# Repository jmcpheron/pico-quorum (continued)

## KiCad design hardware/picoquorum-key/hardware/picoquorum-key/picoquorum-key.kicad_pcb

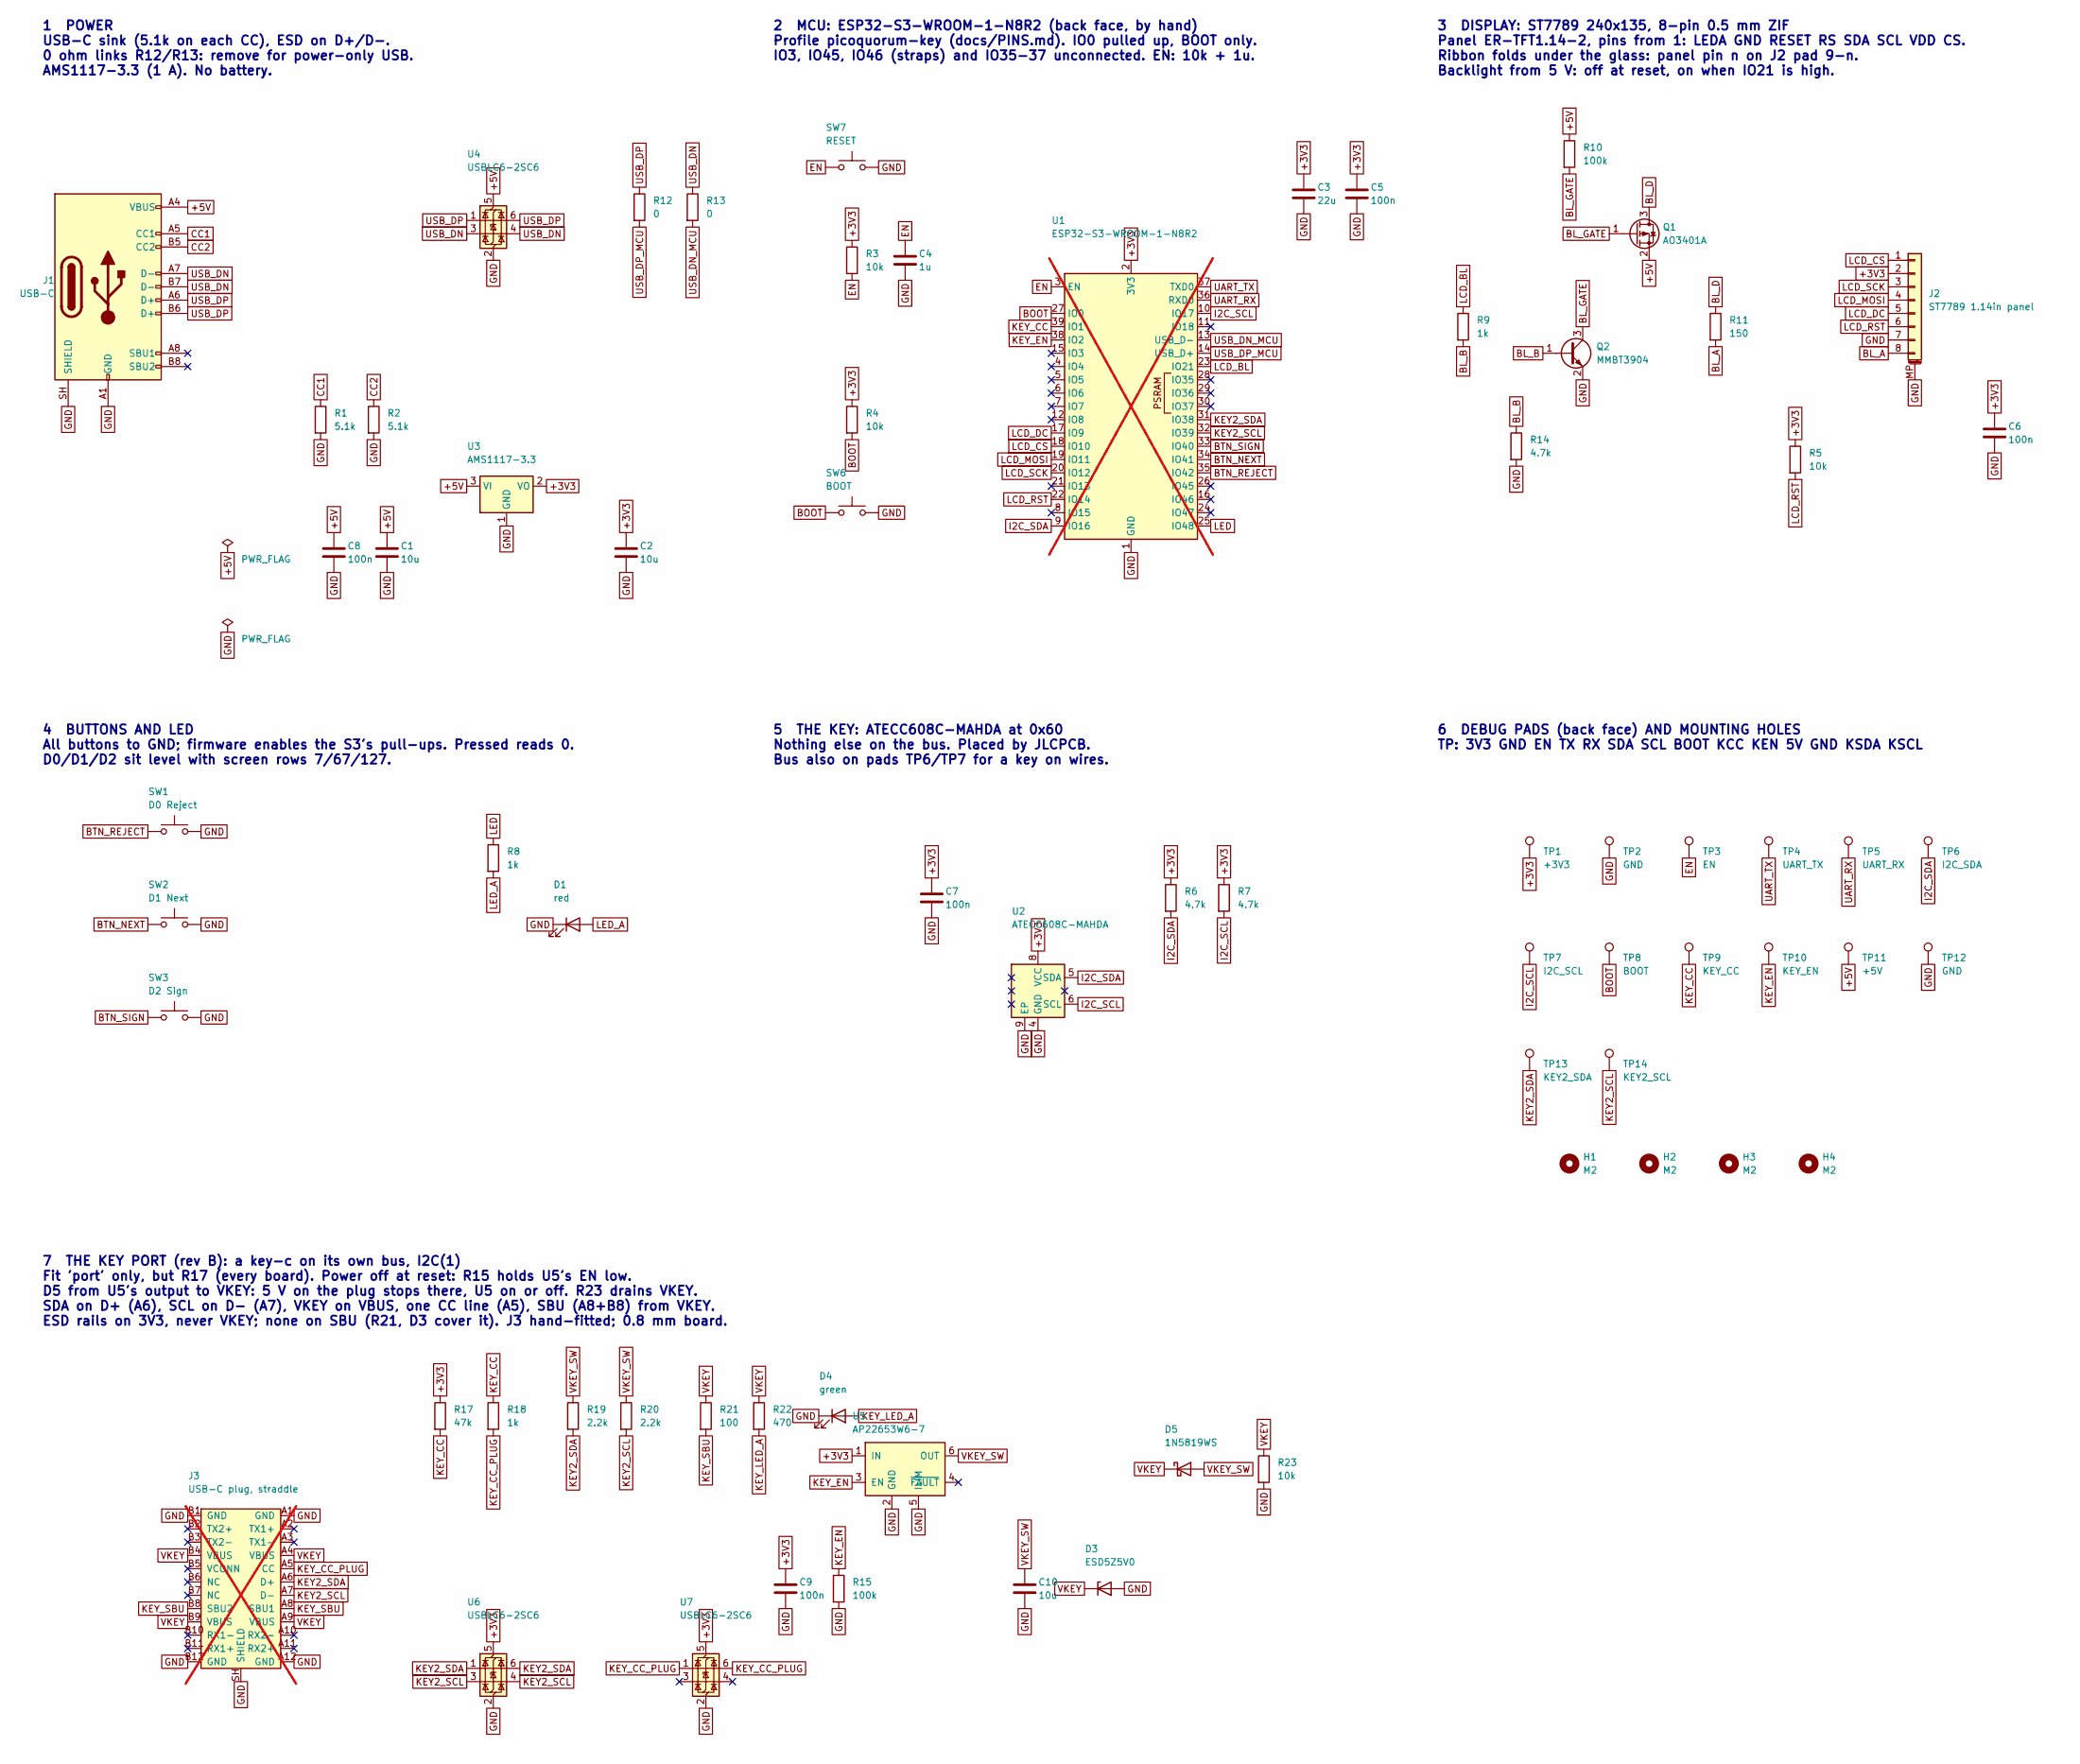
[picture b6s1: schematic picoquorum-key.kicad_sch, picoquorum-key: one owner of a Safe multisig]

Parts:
C1, C2, C10: 10u; C_0805_2012Metric; MPN 10u; LCSC C15850
C3: 22u; C_0805_2012Metric; MPN 22u; LCSC C45783
C4: 1u; C_0603_1608Metric; MPN 1u; LCSC C15849
C5, C6, C7, C8, C9: 100n; C_0603_1608Metric; MPN 100n; LCSC C14663
D1: red; LED_0603_1608Metric; MPN KT-0603R; LCSC C2286
D3: ESD5Z5V0; D_SOD-523; MPN ESD5Z5V0; LCSC C502546
D4: green; LED_0603_1608Metric; MPN KT-0603G; LCSC C12624
D5: 1N5819WS; D_SOD-323; MPN 1N5819WS; LCSC C191023
H1, H2, H3, H4: M2; MountingHole_2.2mm_M2; MPN M2
J1: USB-C; USB_C_Receptacle_HRO_TYPE-C-31-M-12_Edge; MPN HRO TYPE-C-31-M-12; LCSC C165948
J2: ST7789 1.14in panel; FPC_0.5mm_8P_C2919492; MPN HDGC 0.5K-HX-8PWB; LCSC C2919492
J3: USB-C plug, straddle; USB_C_Plug_ShouHan_24P-GTJB_Straddle; MPN TYPE-C 24P-GTJB 040; LCSC C3151751; not fitted
Q1: AO3401A; SOT-23; MPN AO3401A; LCSC C15127
Q2: MMBT3904; SOT-23; MPN MMBT3904; LCSC C20526
R1, R2: 5.1k; R_0603_1608Metric; MPN 5.1k; LCSC C23186
R3, R4, R5, R23: 10k; R_0603_1608Metric; MPN 10k; LCSC C25804
R6, R7, R14: 4.7k; R_0603_1608Metric; MPN 4.7k; LCSC C23162
R8, R9, R18: 1k; R_0603_1608Metric; MPN 1k; LCSC C21190
R10, R15: 100k; R_0603_1608Metric; MPN 100k; LCSC C25803
R11: 150; R_0603_1608Metric; MPN 150; LCSC C22808
R12, R13: 0; R_0603_1608Metric; MPN 0; LCSC C21189
R17: 47k; R_0603_1608Metric; MPN 47k; LCSC C25819
R19, R20: 2.2k; R_0603_1608Metric; MPN 2.2k; LCSC C4190
R21: 100; R_0603_1608Metric; MPN 100; LCSC C22775
R22: 470; R_0603_1608Metric; MPN 470; LCSC C23179
SW1: D0 Reject; SW_Tact_4.5x4.5_C2897501; MPN BOOMELE 4.5x4.5x3.8 SMD tact; LCSC C2897501
SW2: D1 Next; SW_Tact_4.5x4.5_C2897501; MPN BOOMELE 4.5x4.5x3.8 SMD tact; LCSC C2897501
SW3: D2 Sign; SW_Tact_4.5x4.5_C2897501; MPN BOOMELE 4.5x4.5x3.8 SMD tact; LCSC C2897501
SW6: BOOT; SW_Tact_4.5x4.5_C2897501; MPN BOOMELE 4.5x4.5x3.8 SMD tact; LCSC C2897501
SW7: RESET; SW_Tact_4.5x4.5_C2897501; MPN BOOMELE 4.5x4.5x3.8 SMD tact; LCSC C2897501
TP1: +3V3; TestPoint_Pad_1.5x1.5mm; MPN +3V3
TP2, TP12: GND; TestPoint_Pad_1.5x1.5mm; MPN GND
TP3: EN; TestPoint_Pad_1.5x1.5mm; MPN EN
TP4: UART_TX; TestPoint_Pad_1.5x1.5mm; MPN UART_TX
TP5: UART_RX; TestPoint_Pad_1.5x1.5mm; MPN UART_RX
TP6: I2C_SDA; TestPoint_Pad_1.5x1.5mm; MPN I2C_SDA
TP7: I2C_SCL; TestPoint_Pad_1.5x1.5mm; MPN I2C_SCL
TP8: BOOT; TestPoint_Pad_1.5x1.5mm; MPN BOOT
TP9: KEY_CC; TestPoint_Pad_1.5x1.5mm; MPN KEY_CC
TP10: KEY_EN; TestPoint_Pad_1.5x1.5mm; MPN KEY_EN
TP11: +5V; TestPoint_Pad_1.5x1.5mm; MPN +5V
TP13: KEY2_SDA; TestPoint_Pad_1.5x1.5mm; MPN KEY2_SDA
TP14: KEY2_SCL; TestPoint_Pad_1.5x1.5mm; MPN KEY2_SCL
U1: ESP32-S3-WROOM-1-N8R2; ESP32-S3-WROOM-1_HandSolder; MPN ESP32-S3-WROOM-1-N8R2; LCSC C2913204; not fitted
U2: ATECC608C-MAHDA; DFN-8-1EP_3x2mm_P0.5mm_EP1.3x1.5mm; MPN ATECC608C-MAHDA-S; LCSC C23291019
U3: AMS1117-3.3; SOT-223-3_TabPin2; MPN AMS1117-3.3; LCSC C6186
U4, U6, U7: USBLC6-2SC6; SOT-23-6; MPN USBLC6-2SC6; LCSC C7519
U5: AP22653W6-7; SOT-23-6; MPN AP22653W6-7; LCSC C2158037

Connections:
+3V3: C2.1, C3.1, C5.1, C6.1, C7.1, C9.1, J2.2, R3.1, R4.1, R5.1, R6.1, R7.1, R17.1, TP1.1, U1.2 (3V3), U2.8 (VCC), U3.2 (VO), U5.1 (IN), U6.5 (VBUS), U7.5 (VBUS)
+5V: C1.1, C8.1, J1.A4 (VBUS), J1.A9 (VBUS), J1.B4 (VBUS), J1.B9 (VBUS), Q1.2 (S), R10.1, TP11.1, U3.3 (VI), U4.5 (VBUS)
BL_A: J2.8, R11.2
BL_B: Q2.1 (B), R9.2, R14.1
BL_D: Q1.3 (D), R11.1
BL_GATE: Q1.1 (G), Q2.3 (C), R10.2
BOOT: R4.2, SW6.1, TP8.1, U1.27 (IO0)
BTN_NEXT: SW2.1, U1.34 (IO41)
BTN_REJECT: SW1.1, U1.35 (IO42)
BTN_SIGN: SW3.1, U1.33 (IO40)
CC1: J1.A5 (CC1), R1.1
CC2: J1.B5 (CC2), R2.1
EN: C4.1, R3.2, SW7.1, TP3.1, U1.3 (EN)
GND: C1.2, C2.2, C3.2, C4.2, C5.2, C6.2, C7.2, C8.2, C9.2, C10.2, D1.1 (K), D3.2 (A), D4.1 (K), J1.A1 (GND), J1.A12 (GND), J1.B1 (GND), J1.B12 (GND), J1.SH (SHIELD), J2.7, J2.MP (MountPin), J3.A1 (GND), J3.A12 (GND), J3.B1 (GND), J3.B12 (GND), J3.SH (SHIELD), Q2.2 (E), R1.2, R2.2, R14.2, R15.2, R23.2, SW1.2, SW2.2, SW3.2, SW6.2, SW7.2, TP2.1, TP12.1, U1.1 (GND), U1.40 (GND), U1.41 (GND), U2.4 (GND), U2.9 (EP), U3.1 (GND), U4.2 (GND), U5.2 (GND), U5.5 (ILIM), U6.2 (GND), U7.2 (GND)
I2C_SCL: R7.2, TP7.1, U1.10 (IO17), U2.6 (SCL)
I2C_SDA: R6.2, TP6.1, U1.9 (IO16), U2.5 (SDA)
KEY2_SCL: J3.A7 (D-), R20.2, TP14.1, U1.32 (IO39), U6.3 (I/O2), U6.4 (I/O2)
KEY2_SDA: J3.A6 (D+), R19.2, TP13.1, U1.31 (IO38), U6.1 (I/O1), U6.6 (I/O1)
KEY_CC: R17.2, R18.1, TP9.1, U1.39 (IO1)
KEY_CC_PLUG: J3.A5 (CC), R18.2, U7.1 (I/O1), U7.6 (I/O1)
KEY_EN: R15.1, TP10.1, U1.38 (IO2), U5.3 (EN)
KEY_LED_A: D4.2 (A), R22.2
KEY_SBU: J3.A8 (SBU1), J3.B8 (SBU2), R21.2
LCD_BL: R9.1, U1.23 (IO21)
LCD_CS: J2.1, U1.18 (IO10)
LCD_DC: J2.5, U1.17 (IO9)
LCD_MOSI: J2.4, U1.19 (IO11)
LCD_RST: J2.6, R5.2, U1.22 (IO14)
LCD_SCK: J2.3, U1.20 (IO12)
LED: R8.1, U1.25 (IO48)
LED_A: D1.2 (A), R8.2
UART_RX: TP5.1, U1.36 (RXD0)
UART_TX: TP4.1, U1.37 (TXD0)
USB_DN: J1.A7 (D-), J1.B7 (D-), R13.1, U4.3 (I/O2), U4.4 (I/O2)
USB_DN_MCU: R13.2, U1.13 (USB_D-)
USB_DP: J1.A6 (D+), J1.B6 (D+), R12.1, U4.1 (I/O1), U4.6 (I/O1)
USB_DP_MCU: R12.2, U1.14 (USB_D+)
VKEY: D3.1 (K), D5.1 (K), J3.A4 (VBUS), J3.A9 (VBUS), J3.B4 (VBUS), J3.B9 (VBUS), R21.1, R22.1, R23.1
VKEY_SW: C10.1, D5.2 (A), R19.1, R20.1, U5.6 (OUT)

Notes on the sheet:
1 POWER USB-C sink (5.1k on each CC), ESD on D+/D-. 0 ohm links R12/R13: remove for power-only USB. AMS1117-3.3 (1 A). No battery.
2 MCU: ESP32-S3-WROOM-1-N8R2 (back face, by hand) Profile picoquorum-key (docs/PINS.md). IO0 pulled up, BOOT only. IO3, IO45, IO46 (straps) and IO35-37 unconnected. EN: 10k + 1u.
3 DISPLAY: ST7789 240x135, 8-pin 0.5 mm ZIF Panel ER-TFT1.14-2, pins from 1: LEDA GND RESET RS SDA SCL VDD CS. Ribbon folds under the glass: panel pin n on J2 pad 9-n. Backlight from 5 V: off at reset, on when IO21 is high.
4 BUTTONS AND LED All buttons to GND; firmware enables the S3's pull-ups. Pressed reads 0. D0/D1/D2 sit level with screen rows 7/67/127.
5 THE KEY: ATECC608C-MAHDA at 0x60 Nothing else on the bus. Placed by JLCPCB. Bus also on pads TP6/TP7 for a key on wires.
6 DEBUG PADS (back face) AND MOUNTING HOLES TP: 3V3 GND EN TX RX SDA SCL BOOT KCC KEN 5V GND KSDA KSCL
7 THE KEY PORT (rev B): a key-c on its own bus, I2C(1) Fit 'port' only, but R17 (every board). Power off at reset: R15 holds U5's EN low. D5 from U5's output to VKEY: 5 V on the plug stops there, U5 on or off. R23 drains VKEY. SDA on D+ (A6), SCL on D- (A7), VKEY on VBUS, one CC line (A5), SBU (A8+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

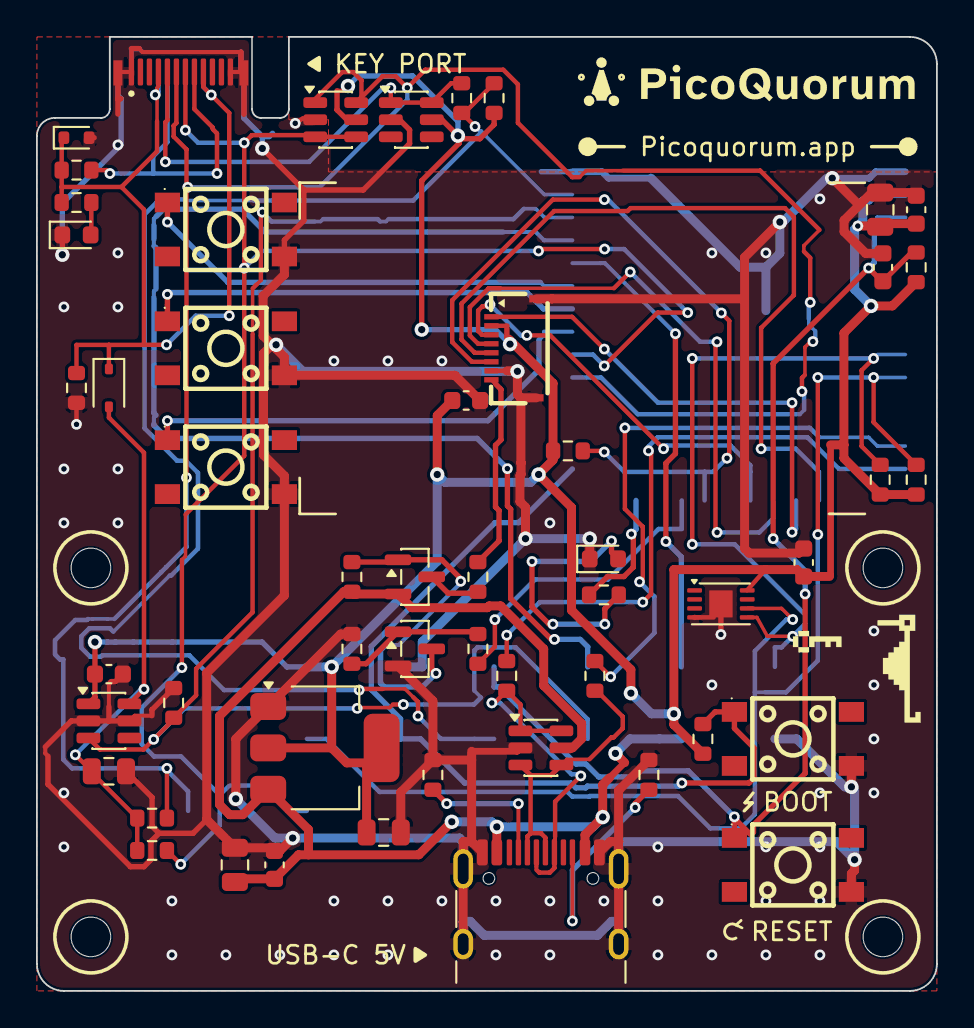
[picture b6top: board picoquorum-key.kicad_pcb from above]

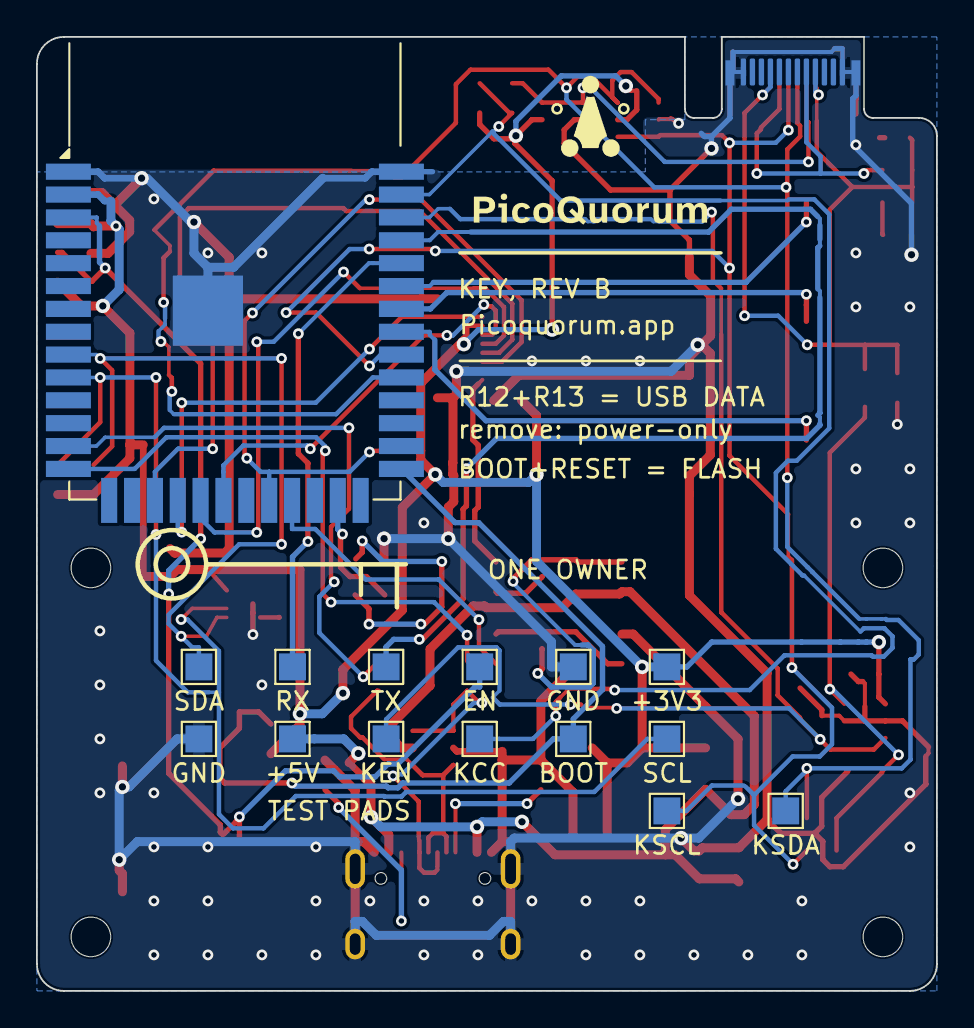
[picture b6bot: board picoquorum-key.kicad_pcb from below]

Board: 2 copper layers, 50.0 x 53.0 mm, 71 parts (15 on the bottom side), 39 nets.

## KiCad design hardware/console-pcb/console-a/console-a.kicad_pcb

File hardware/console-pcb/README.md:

# Console PCB, concept 1

The separate [M1 prototype carrier](../console-pcb-m1/README.md) has a 1.3 inch
colour LCD module, eight SMT buttons, a Pico 2 W module and internal key-adapter
pads. Its routed KiCad files and manufacturing quote package are separate from
the earlier knob/dock concept and CAD studies below.

2026-10-07. **Design in progress, not fabrication files.** A controls subcircuit and
native KiCad placement study now exist. The complete schematic, routing, physical fit
and hardware tests are unfinished. Do not order from these drafts.

Start with [component research and CAD status](RESEARCH.md). The
[controls drawing](review/controls.svg) comes from `controls.kicad_sch`; the
[placement drawing](review/placement.svg) comes from `placement-study.kicad_pcb`.
They are separate studies, not a schematic/PCB pair ready for manufacturing.

The chosen direction is a colour screen, a rotary knob, and a USB-C key dock. Favour
straightforward assembly and supported parts over the lowest component price. Start with
external power and no battery. Quantities to quote later: 5 prototypes, 20 and 100 consoles.

## Face and case

The sketch proposes a 130 x 110 mm case and a 120 x 100 mm main PCB. These are layout
allowances, not measured component fits. Case height is open until the display, plug,
encoder and Pico stack is drawn in section. The face is horizontal for this first study.

| item | proposed allowance | detail still to settle |
|---|---|---|
| Screen, left | 70 x 51 mm panel envelope | 2.8 inch colour, 320 x 240 landscape; exact panel and ribbon exit |
| Knob, right | 24 mm diameter cap | shaft length, detents, push force and support |
| Key dock, back right | 22 x 25 mm footprint | upright insertion; pocket must fit the final key case |
| Sign and Reject, front left | 12 mm button caps | Sign recessed behind a rim; Reject unobstructed |
| Back and Device, front right | two smaller buttons | preserve B and X functions while the UI is reviewed |
| Power, back | USB-C female socket | separate from the male key dock; label POWER |

The ordered key is a 16 x 36 mm PCB with a female connector. It stands upright in this
proposal. Its case, finger clearance and insertion path need a side-view fit study. The
dock footprint is not the key's full height. Do not change the ordered P2 key board.

Support the key case with guide walls. Keep the plug below their rim. Use a stop and
clearance stack based on the connector's mating drawing: the pocket must allow full
mating without forcing the connector past its travel. Allow easy one-hand removal;
no locking latch in this revision. Support the main PCB near the plug and encoder.
The solder pads must not be the only path for insertion or sideways loads.

The panel mounts to the case with a compliant support. Insert its ribbon into a locking
connector after soldering. Do not load the glass or fold its ribbon sharply. Place the
Pico antenna at an enclosure edge, with the manufacturer's copper/component keepout and
clearance from the display, key, metal knob and case hardware. The sketch does not place
the Pico or establish that these clearances fit.

## Parts to evaluate

These are candidates and requirements, not a purchasing BOM. Stock, full order codes,
footprints, assembly availability and mating dimensions remain to be checked.

| function | candidate or requirement | reason / open point |
|---|---|---|
| Processor | Raspberry Pi Pico 2 W, without headers | existing firmware; castellated carrier mounting; assembler must accept the module and thermal process |
| Encoder | Bourns PEC11J, detented version with push switch | SMD; choose full shaft/detent/switch code after a feel sample |
| Key plug | GCT USB4151 vertical Type-C plug family | documented docking part; 24 contacts, SMD signal terminals and through-hole shell stakes; confirm exact version and process |
| Screen | 2.8 inch, 240 x 320 native, four-wire SPI ST7789, no touch | prefer wide viewing angles and a locking FPC connector; exact part unselected |
| Screen comparison | EastRising ER-TFT028A3-4 | documented plug-in FPC and 50.20 x 69.30 mm outline; directional viewing, so not an IPS selection |
| Buttons | documented SMT tactile switches and case-held caps | separate A, B, X and Y; full part and actuation force open |
| Power input | USB-C receptacle, 5 V sink, no PD negotiation | independent Rd on each CC; input protection and current budget needed |
| Key power | current-limited, reverse-blocking switch, default off | TPS2553 family is a comparison candidate, not selected; its 75 mA typical lower limit and fault behaviour require review |
| Bus protection | bidirectional isolation with powered-off and foreign-voltage protection, plus connector ESD protection | exact parts open; preserve ATECC wake timing and open-drain signalling |

The PEC11J datasheet specifies 100,000 rotational cycles and 20,000 switch cycles. It
calls for one reflow pass, discourages hand soldering, and does not recommend aqueous
washing. Agree the assembly sequence before layout. A mostly single-side assembly is
a goal, not a constraint that overrides mechanical support or antenna clearance.

The working encoder choice is now PEC11J-9215F-S0015; its 30 detents / 15 pulses
need a click-count check with the current driver. The four working button choices
are TL3305AF160QG. Full findings and assembly limits are in [RESEARCH.md](RESEARCH.md).
The USB4151 drawing specifies a 0.8 mm board. A small supported dock board is under
consideration so the main board can stay 1.6 mm; its stack and internal connection
are not yet designed.

The display comparison part lists 2.8 V typical supply and 70 mA typical backlight
current. It is not a drop-in replacement for the bench display module. Check logic
levels, supply limits, SPI mode straps and LED wiring in the exact datasheet before
choosing regulators or a backlight driver. GP13 controls the driver; it does not power
the LED string. A new panel still needs colour, orientation and readability checks.

## Circuit blocks

```text
Rear POWER socket (5 V)
    -> input protection and supply isolation -> Pico VSYS
    -> display supplies / backlight driver (after panel selection)

Pico 3V3 -> default-off, current-limited, reverse-blocking switch -> KEY_VCC
KEY_VCC -> dock VBUS; controlled discharge; key-side bus pull-ups

GP4/GP5 <-> protected, isolatable I2C path <-> dock D+/D- <-> key SDA/SCL
Dock attachment contacts -> protected sensing -> presence / fault handling
GP6 -> key power request; hardware fault conditions must override it

GP8..GP13 -> display control and SPI; GP13 -> backlight driver control
GP3/GP2/GP1 <- encoder A/B/push
GP15/GP17/GP19/GP21 <- Sign/Back/Device/Reject
```

This is a functional diagram, not a wireable schematic. Check the Pico regulator's
available current under Wi-Fi load before assigning display and key loads to 3V3.
Keep a service route to Pico BOOTSEL, RUN and SWD. If Pico micro-USB remains accessible,
the external supply arrangement must tolerate both power inputs without backfeeding.

### The key port

The port uses Type-C mechanics but carries I2C and switched 3.3 V, not USB data or a
standard USB power-source interface. Never connect dock VBUS straight to GP6, 3V3 or 5 V.

The existing [socket-and-cable proposal](../key-pcb/PROPOSALS.md#the-console-end-of-key-c)
is background, not a direct-plug schematic. A plug has CC/VCONN roles that differ from
a receptacle's CC1/CC2 arrangement. Trace the selected plug and the P2 receptacle pin
by pin, in both orientations. Do not copy the rule "exactly one Rd" from the cable
proposal without establishing what this mating pair actually exposes. Do not tie
attachment-sense contacts together or energize VCONN by assumption.

Required behaviour:

- Power and bus drive default off during reset, boot, removal and fault.
- Stable attachment permits controlled power-up. It does not authenticate a key or
  prove full mechanical seating. Confirm the chip and reject unsupported devices.
- Removal cancels an unfinished approval, cuts power and releases the bus. Reinserted
  keys must not inherit the previous review or hold-to-sign state.
- Limit short-circuit current in hardware. Validate switch tolerance, startup current,
  thermal behaviour and shutdown; do not equate the limit with normal key current.
- Block foreign VBUS from the console supply, both powered and unpowered. A load switch
  alone does not protect SDA, SCL or the attachment-sense inputs.
- Isolate MCU bus pins from externally driven voltages and an unpowered key. Start with
  the earlier 2.2 kohm switched pull-up proposal only as a value to calculate and measure.
  External VBUS must not turn those pull-ups into a path to an unprotected GPIO.
- Protect exposed contacts against ESD. ESD suppression is not sustained overvoltage
  protection. Specify the charger/adapter fault envelope before choosing devices.
- Controlled discharge must not short an externally powered VBUS. Check this explicitly.

## Proposed GPIO reservation

Preserve current `firmware/board.py` assignments where possible. Nothing changes firmware
in this draft. In particular, the knob A/B naming below follows the current driver,
whose ordering differs from the older breadboard labels.

| GPIO | proposed function |
|---|---|
| 1 | encoder push; maintenance at boot |
| 3, 2 | encoder A, B; verify direction and steps per detent on selected part |
| 4, 5 | key SDA, SCL through protection |
| 6 | key power request, external default-off bias |
| 7 | reserved for attachment/fault logic |
| 8, 9, 10, 11, 12, 13 | display DC, CS, SCK, MOSI, RESET, backlight control |
| 15, 17, 19, 21 | A/Sign, B/Back, X/Device, Y/Reject; Y also Wi-Fi setup at boot |
| 26, 27 | reserve for protected attachment sensing if analog sensing is chosen |
| 28 | spare analog input; no battery in this revision |

GP26/27 are reassigned from the old Build 1 Trust M reset / key-ID plan. Do not use
this draft with that harness. No console signing, key provisioning or lock behaviour
changes are authorized by this design document.

## Before a manufacturing quote

1. Select the exact display, plug, encoder and switches. Obtain drawings and check
   assembler stock or sourcing, packaging and solder process. Resolve the power budget.
2. Draw the electrical schematic, including the actual plug pin map and all fault paths.
   Review every powered/unpowered combination and check the firmware work required.
3. Draw the mechanical stack and print a dock/knob fit sample. Check actual key-case fit,
   full connector engagement, removal, board flex and antenna clearance.
4. Route the PCB with mounting holes, test access and source-location silkscreen. Run
   ERC, DRC, connectivity and schematic/PCB parity checks; inspect footprints and 3D fit.
5. Export Gerbers, drills, BOM, placement file, assembly drawings and STEP models. Quote
   5/20/100 separately, including module installation, screen insertion, enclosure,
   programming and testing. A quote is not permission to place an order.

Before a production batch, bench-check controlled startup, short and foreign-power
faults, hot removal, both key orientations, bus rise time and wake timing. Exercise the
complete review/reject/hold-to-sign flow on test keys. Do not provision, lock or write
hardware without a separate explicit request. The signing site remains `quorum.sign_it`.

## Sources and checks

Manufacturer pages checked 2026-10-07:

- [Pico 2 W](https://www.raspberrypi.com/products/raspberry-pi-pico-2/?variant=pico-2-w).
- [PEC11J datasheet](https://www.bourns.com/docs/product-datasheets/pec11j.pdf).
- [GCT plug selector](https://gct.co/usb-connector/usb-plug) and
  [USB4151 introduction](https://gct.co/news/gct-launches-vertical-mount-usb-type-c-plug-aimed-at-docking-designs).
- [Display comparison](https://www.buydisplay.com/2-8-inch-tft-lcd-display-capacitive-touch-screen-st7789v-spi-240x320).
- [TPS2553 family datasheet](https://www.ti.com/lit/ds/symlink/tps2553.pdf).

Read against the repository README, hardware notes, ordered key-C P2 description,
Build 1 pin map, `firmware/board.py`, `firmware/knob.py` and console button handling.
The concept drawing is an editable SVG. Its panel and control shapes are layout
envelopes, not component footprints. See [CHECKS.md](CHECKS.md) for the controls ERC,
placement DRC findings and the checks still missing. No supplier stock, assembly
quote, circuit simulation, physical fit or hardware behaviour has been verified.

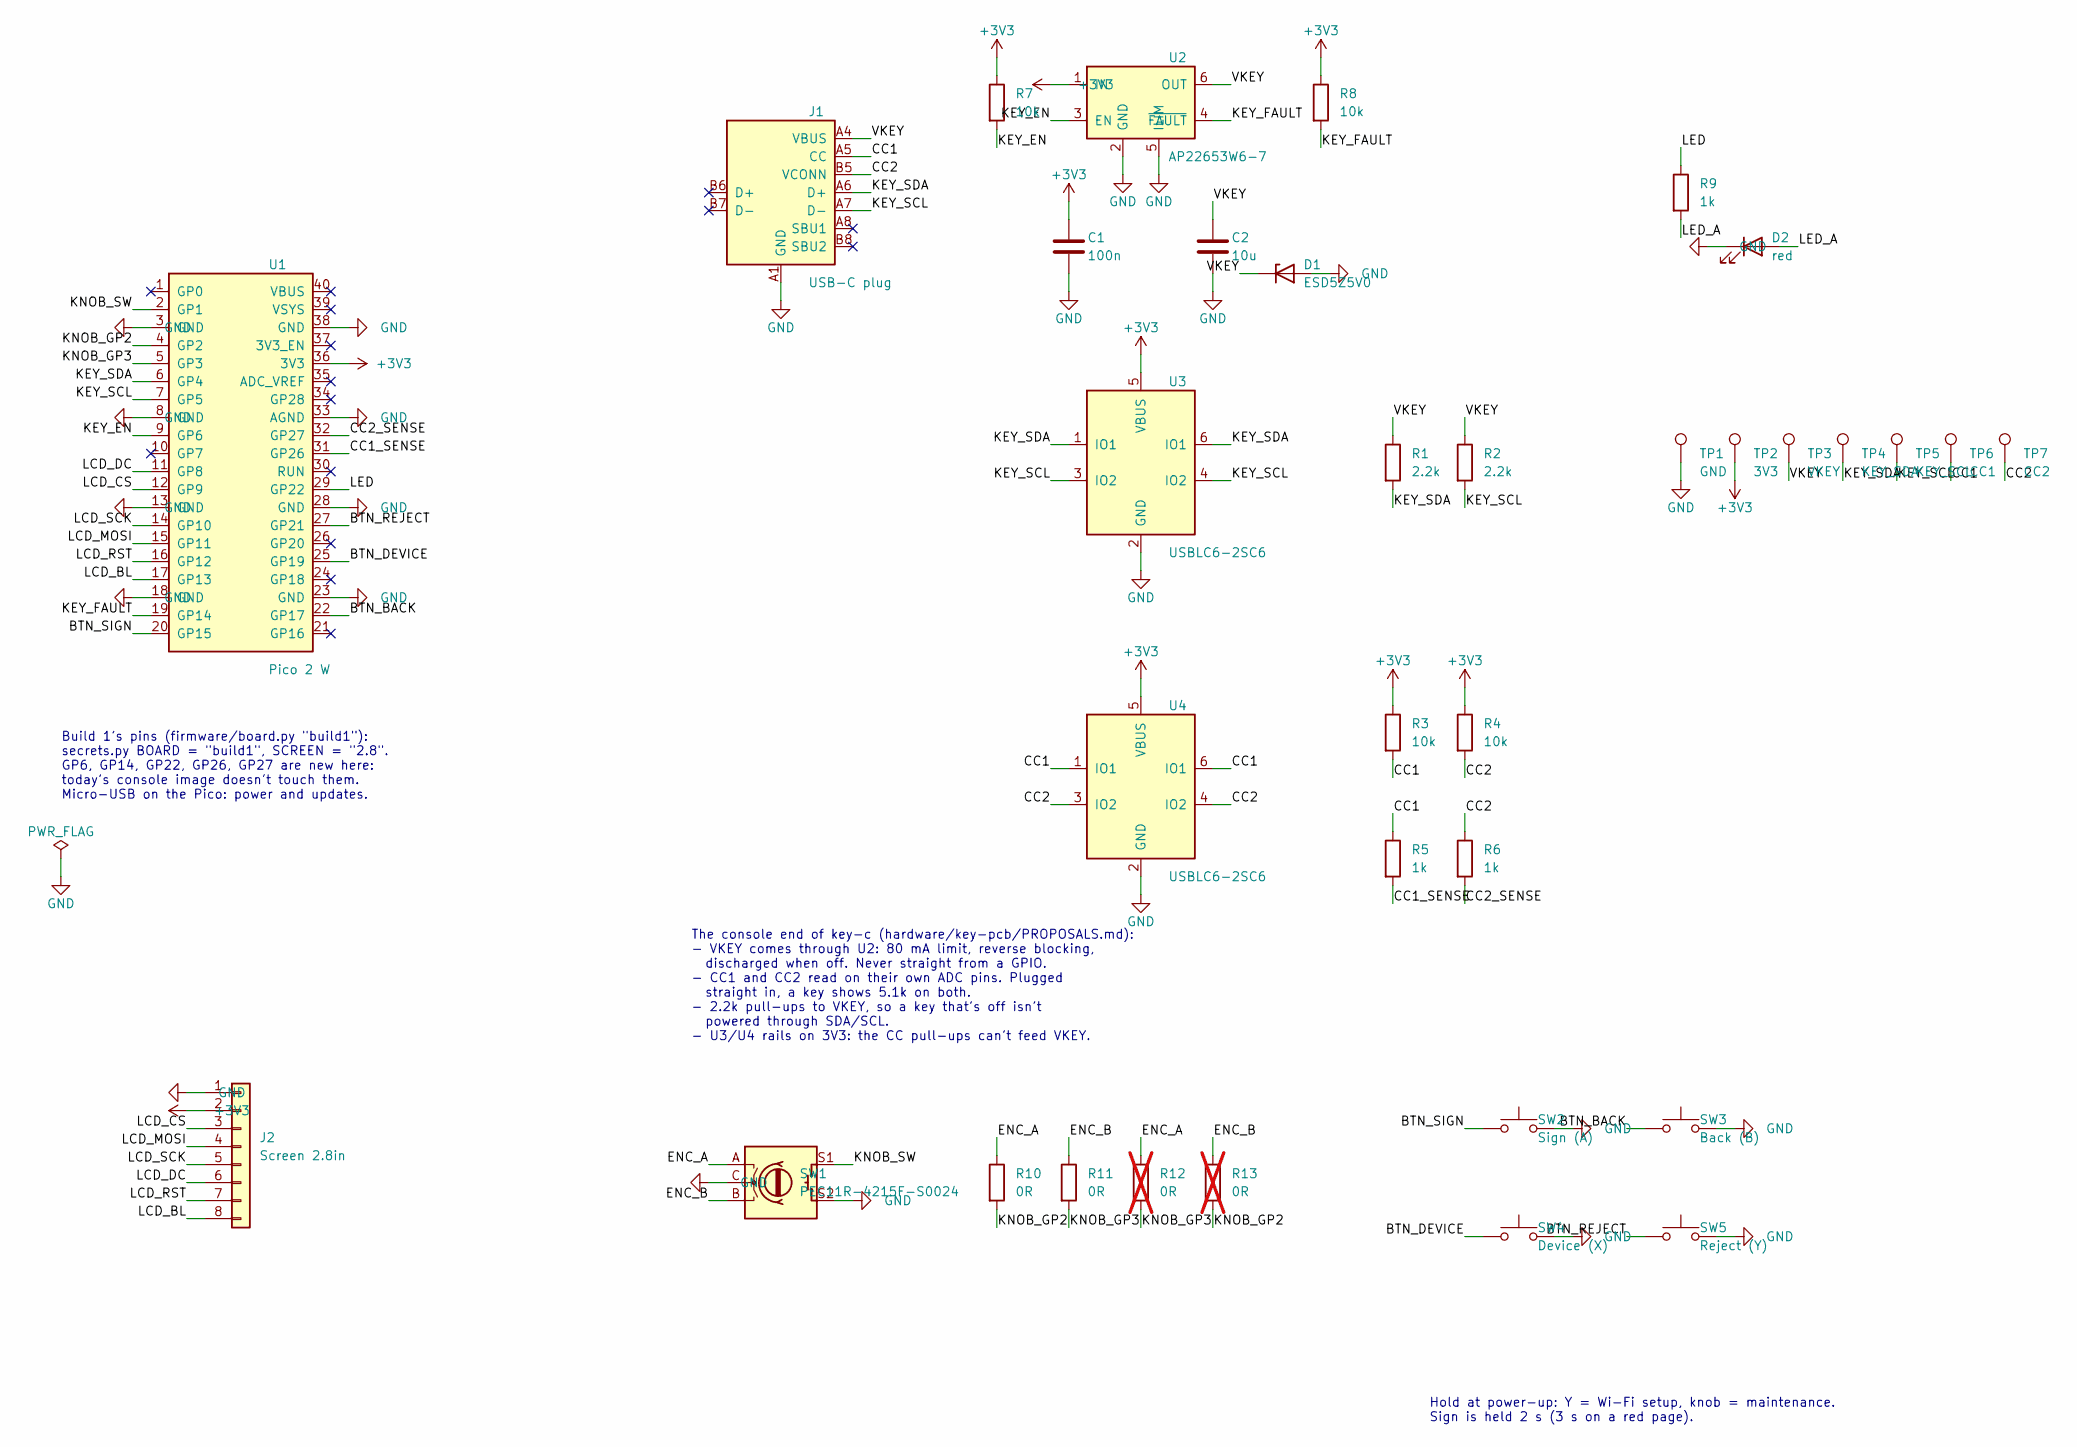
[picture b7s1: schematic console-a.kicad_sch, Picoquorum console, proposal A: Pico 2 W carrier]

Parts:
C1: 100n; C_0402_1005Metric; LCSC C1525
C2: 10u; C_0603_1608Metric; LCSC C19702
D1: ESD5Z5V0; D_SOD-523; MPN ESD5Z5V0; LCSC C502546
D2: red; LED_0603_1608Metric; MPN KT-0603R; LCSC C2286
J1: USB-C plug; USB_C_Plug_ShenzhenJingTuoJin_918-118A2021Y40002_Vertical; MPN 918-118A2021Y40002; LCSC C399939
J2: Screen 2.8in; Screen_ST7789_2.8in_8P_PLACEHOLDER; MPN 2.8in 240x320 ST7789 SPI module, 8-pin
R1, R2: 2.2k; R_0402_1005Metric; LCSC C25879
R3, R4, R7, R8: 10k; R_0402_1005Metric; LCSC C25744
R5, R6, R9: 1k; R_0402_1005Metric; LCSC C11702
R10, R11: 0R; R_0402_1005Metric; LCSC C17168
R12, R13: 0R; R_0402_1005Metric; LCSC C17168; not fitted
SW1: PEC11R-4215F-S0024; RotaryEncoder_Bourns_PEC11R-S_Vertical; MPN PEC11R-4215F-S0024
SW2: Sign (A); SW_HRO_K2-1102SP_6x6mm; MPN K2-1102SP-K4SC-04; LCSC C129461
SW3: Back (B); SW_HRO_K2-1102SP_6x6mm; MPN K2-1102SP-K4SC-04; LCSC C129461
SW4: Device (X); SW_HRO_K2-1102SP_6x6mm; MPN K2-1102SP-K4SC-04; LCSC C129461
SW5: Reject (Y); SW_HRO_K2-1102SP_6x6mm; MPN K2-1102SP-K4SC-04; LCSC C129461
TP1: GND; TestPoint_Pad_D1.5mm
TP2: 3V3; TestPoint_Pad_D1.5mm
TP3: VKEY; TestPoint_Pad_D1.5mm
TP4: KEY_SDA; TestPoint_Pad_D1.5mm
TP5: KEY_SCL; TestPoint_Pad_D1.5mm
TP6: CC1; TestPoint_Pad_D1.5mm
TP7: CC2; TestPoint_Pad_D1.5mm
U1: Pico 2 W; RaspberryPi_Pico_2_W_SMD_PQ; MPN Raspberry Pi Pico 2 W (SC1633); LCSC C42394205
U2: AP22653W6-7; SOT-23-6; MPN AP22653W6-7; LCSC C2158037
U3, U4: USBLC6-2SC6; SOT-23-6; MPN USBLC6-2SC6; LCSC C7519

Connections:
+3V3: C1.1, J2.2, R3.1, R4.1, R7.1, R8.1, TP2.1, U1.36 (3V3), U2.1 (IN), U3.5 (VBUS), U4.5 (VBUS)
/BTN_BACK: SW3.1, U1.22 (GP17)
/BTN_DEVICE: SW4.1, U1.25 (GP19)
/BTN_REJECT: SW5.1, U1.27 (GP21)
/BTN_SIGN: SW2.1, U1.20 (GP15)
/CC1: J1.A5 (CC), R3.2, R5.1, TP6.1, U4.1 (IO1), U4.6 (IO1)
/CC1_SENSE: R5.2, U1.31 (GP26)
/CC2: J1.B5 (VCONN), R4.2, R6.1, TP7.1, U4.3 (IO2), U4.4 (IO2)
/CC2_SENSE: R6.2, U1.32 (GP27)
/ENC_A: R10.1, R12.1, SW1.A
/ENC_B: R11.1, R13.1, SW1.B
/KEY_EN: R7.2, U1.9 (GP6), U2.3 (EN)
/KEY_FAULT: R8.2, U1.19 (GP14), U2.4 (~FAULT)
/KEY_SCL: J1.A7 (D-), R2.2, TP5.1, U1.7 (GP5), U3.3 (IO2), U3.4 (IO2)
/KEY_SDA: J1.A6 (D+), R1.2, TP4.1, U1.6 (GP4), U3.1 (IO1), U3.6 (IO1)
/KNOB_GP2: R10.2, R13.2, U1.4 (GP2)
/KNOB_GP3: R11.2, R12.2, U1.5 (GP3)
/KNOB_SW: SW1.S1, U1.2 (GP1)
/LCD_BL: J2.8, U1.17 (GP13)
/LCD_CS: J2.3, U1.12 (GP9)
/LCD_DC: J2.6, U1.11 (GP8)
/LCD_MOSI: J2.4, U1.15 (GP11)
/LCD_RST: J2.7, U1.16 (GP12)
/LCD_SCK: J2.5, U1.14 (GP10)
/LED: R9.1, U1.29 (GP22)
/LED_A: D2.2 (A), R9.2
/VKEY: C2.1, D1.1 (K), J1.A4 (VBUS), J1.A9 (VBUS), J1.B4 (VBUS), J1.B9 (VBUS), R1.1, R2.1, TP3.1, U2.6 (OUT)
GND: C1.2, C2.2, D1.2 (A), D2.1 (K), J1.A1 (GND), J1.A12 (GND), J1.B1 (GND), J1.B12 (GND), J1.SH (SHIELD), J2.1, SW1.C, SW1.S2, SW2.2, SW3.2, SW4.2, SW5.2, TP1.1, U1.3 (GND), U1.8 (GND), U1.13 (GND), U1.18 (GND), U1.23 (GND), U1.28 (GND), U1.33 (AGND), U1.38 (GND), U2.2 (GND), U2.5 (ILIM), U3.2 (GND), U4.2 (GND)

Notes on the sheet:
Build 1's pins (firmware/board.py "build1"): secrets.py BOARD = "build1", SCREEN = "2.8". GP6, GP14, GP22, GP26, GP27 are new here: today's console image doesn't touch them. Micro-USB on the Pico: power and updates.
The console end of key-c (hardware/key-pcb/PROPOSALS.md): - VKEY comes through U2: 80 mA limit, reverse blocking, discharged when off. Never straight from a GPIO. - CC1 and CC2 read on their own ADC pins. Plugged straight in, a key shows 5.1k on both. - 2.2k pull-ups to VKEY, so a key that's off is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
Hold at power-up: Y = Wi-Fi setup, knob = maintenance. Sign is held 2 s (3 s on a red page).

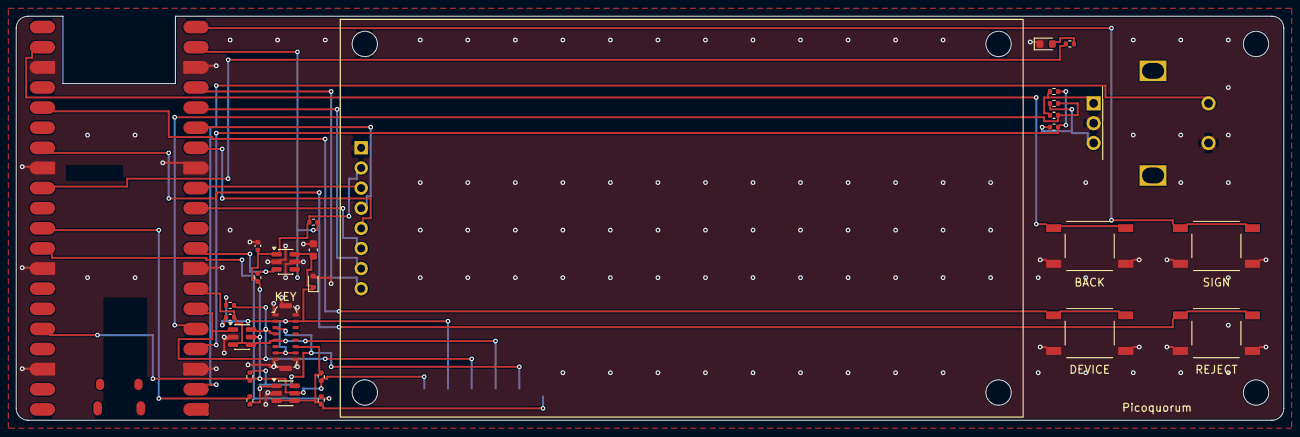
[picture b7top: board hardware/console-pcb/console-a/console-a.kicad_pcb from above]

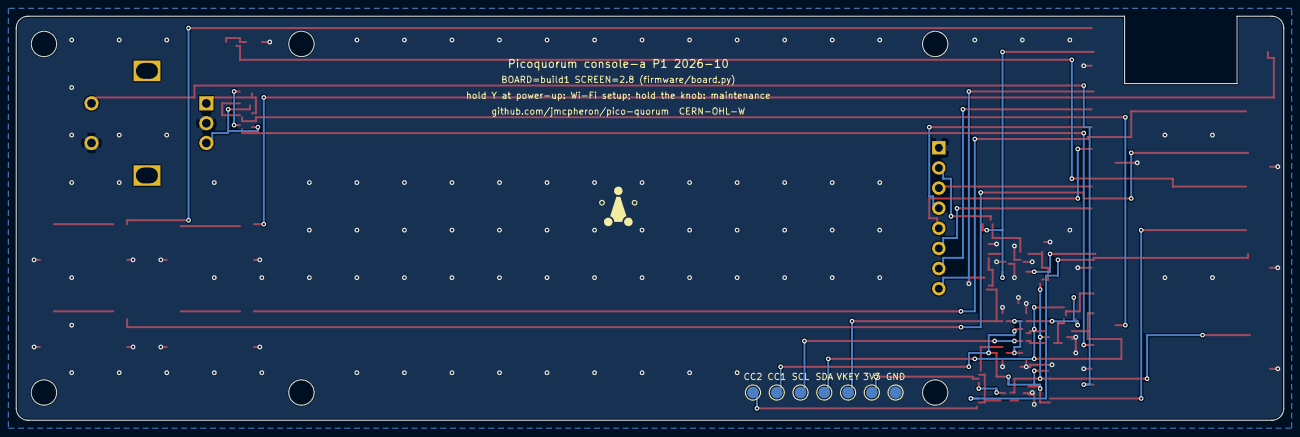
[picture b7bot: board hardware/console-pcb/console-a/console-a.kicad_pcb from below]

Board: 2 copper layers, 160.0 x 51.0 mm, 38 parts (8 on the bottom side), 28 nets.

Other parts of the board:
H2, H3: M3; MountingHole_3.2mm_M3
LOGO1: PicoQuorum_Mark
